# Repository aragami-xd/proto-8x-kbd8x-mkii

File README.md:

## Custom pcb for kbd8x-mkii based on my own personal preference

### Simplified version, less layout, less feature, more clean 

Any recommendations will be ignored and you will be banned, unless you point out fatal flaws in the pcb in which case you can stay

Insta ban if you mention iso support. I may or may not regret this when I find an iso alps board with good condition keycaps

Board dimension, layout and part of the schematics are based on [ai03's kbd8x-mkii's repo](https://github.com/ai03-2725/KBD8X-MKII-PCB), rp2040 routing and schematics are based on [sleepdealer's rpad](https://github.com/Sleepdealr/RPAD)

Todo list:
- ~~Swap out mcu for a different one like rp2040~~ (good luck finding at32u4 for cheap nowadays)
- Add jst connector for shits and giggles (if i can use it for something funny i can yeet out the brass weight and use it)
- ~~Possible alps support? if i can't get blue, amber or brown alps i can go for matias switches~~
- More meme cuts (maybe or maybe not)
- Make pcb thinner, 1.2mm? thinner pcb = easier to millmax / rivet
- ~~jis-alike layout~~: tried, not a good idea
- ~~aek layout~~: aek and 7u layout will be south facing, ~~standard 6.25u layout will be north facing~~ dropped standard layout
- ~~F1-8k layout: REMOVED, check **complex** version of the pcb~~

Layout supports:

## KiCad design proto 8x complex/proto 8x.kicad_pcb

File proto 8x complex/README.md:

## Custom pcb for kbd8x-mkii based on my own personal preference

### Complex version of the pcb, including all layouts supported (still no iso tho)

Any recommendations will be ignored and you will be banned, unless you point out fatal flaws in the pcb in which case you can stay

Insta ban if you mention iso support

Board dimension and layout is based on [ai03's kbd8x-mkii's repo](https://github.com/ai03-2725/KBD8X-MKII-PCB/blob/master), the rest has been reworked from scratch. All credits of the board goes to him and kbdfans

Todo list:
- ~~Swap out mcu for a different one like rp2040~~ (good luck finding at32u4 for cheap nowadays)
- Add jst connector for shits and giggles (if i can use it for something funny i can yeet out the brass weight and use it)
- ~~Possible alps support? if i can't get blue, amber or brown alps i can go for matias switches~~
- More meme cuts (maybe or maybe not)
- Make pcb thinner, 1.2mm? thinner pcb = easier to millmax / rivet
- ~~jis-alike layout~~: tried, not a good idea
- ~~aek layout~~: aek and 7u layout will be south facing, standard 6.25u layout will be north facing
- ~~F1-8k layout~~

Layout supports:

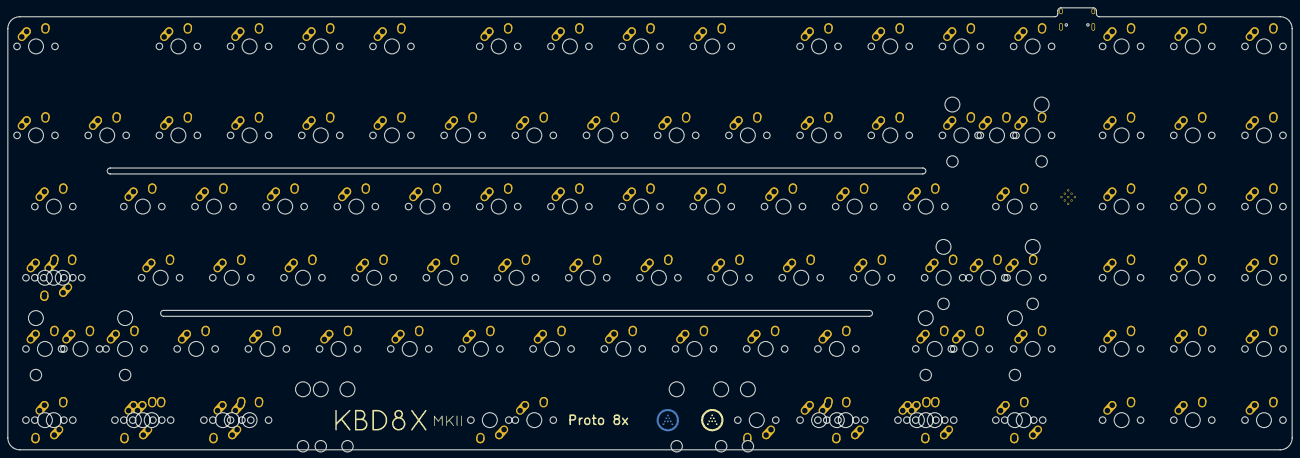
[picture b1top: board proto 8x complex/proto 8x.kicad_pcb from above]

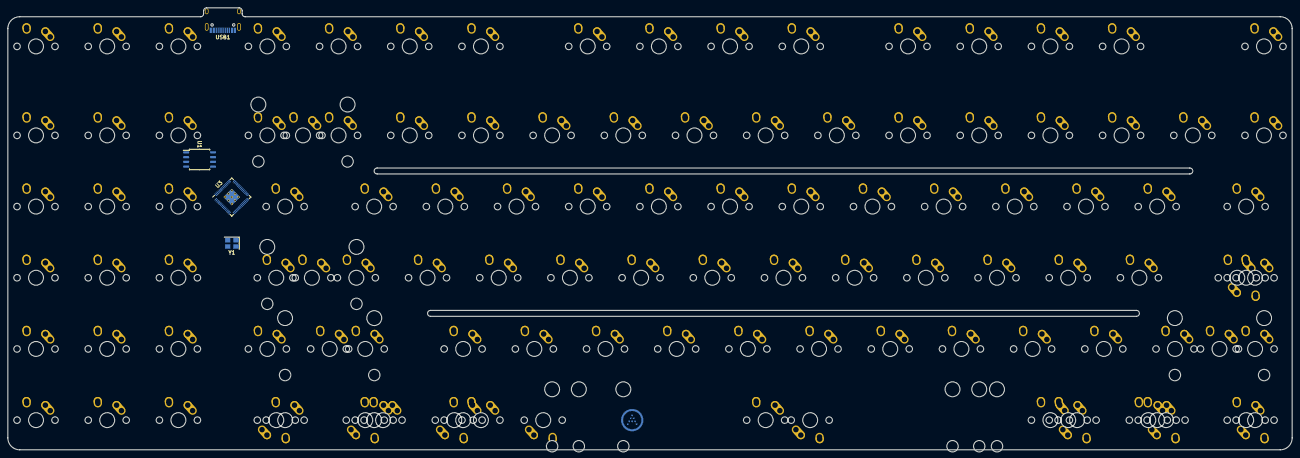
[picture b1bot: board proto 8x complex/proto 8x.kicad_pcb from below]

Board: 2 copper layers, 343.7 x 118.3 mm, 118 parts (4 on the bottom side), 6 nets, no tracks yet.

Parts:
MX_#0_1, MX_#1, MX_#2, MX_#3, MX_#4, MX_#5, MX_#6, MX_#7, MX_#8, MX_#9: MX-1U; MX-1U-NoLED
MX_'1: MX-1U; MX-1U-NoLED
MX_,1: MX-1U; MX-1U-NoLED
MX_-1: MX-1U; MX-1U-NoLED
MX_.1: MX-1U; MX-1U-NoLED
MX_/1: MX-1U; MX-1U-NoLED
MX_;1: MX-1U; MX-1U-NoLED
MX_=1: MX-1U; MX-1U-NoLED
MX_A1: MX-1U; MX-1U-NoLED
MX_B1: MX-1U; MX-1U-NoLED
MX_BACK1: MX-2U; MX-2U-ReversedStabilizers-NoLED
MX_BACK2, MX_BACK3: MX-1U; MX-1U-NoLED
MX_C1: MX-1U; MX-1U-NoLED
MX_CLOCK1: MX-1.75U; MX-1.75U-NoLED
MX_CLOCK2: MX-1.25U; MX-1.25U-NoLED
MX_CLOCK3: MX-1.5U; MX-1.5U-NoLED
MX_D1: MX-1U; MX-1U-NoLED
MX_DEL1_NP7: MX-1U; MX-1U-NoLED
MX_DN1_NP0: MX-1U; MX-1U-NoLED
MX_E1: MX-1U; MX-1U-NoLED
MX_END1_NP8: MX-1U; MX-1U-NoLED
MX_ESC1: MX-1U; MX-1U-NoLED
MX_F1: MX-1U; MX-1U-NoLED
MX_FN1, MX_FN2, MX_FN3, MX_FN4, MX_FN5, MX_FN6, MX_FN7, MX_FN8, MX_FN9, MX_FN10, MX_FN11, MX_FN12: MX-1U; MX-1U-NoLED
MX_G1: MX-1U; MX-1U-NoLED
MX_H1: MX-1U; MX-1U-NoLED
MX_HOME1: MX-1U; MX-1U-NoLED
MX_I1: MX-1U; MX-1U-NoLED
MX_INS1: MX-1U; MX-1U-NoLED
MX_J1: MX-1U; MX-1U-NoLED
MX_K1: MX-1U; MX-1U-NoLED
MX_L1: MX-1U; MX-1U-NoLED
MX_LALT1: MX-1.25U; MX-1.25U-NoLED
MX_LALT2, MX_LALT3: MX-1.5U; MX-1.5U-NoLED
MX_LCTRL1: MX-1.25U; MX-1.25U-NoLED
MX_LCTRL2: MX-1.5U; MX-1.5U-NoLED
MX_LFT1_NP00: MX-1U; MX-1U-NoLED
MX_LGUI1: MX-1.25U; MX-1.25U-NoLED
MX_LGUI2, MX_LGUI3: MX-1U; MX-1U-NoLED
MX_LSHIFT1: MX-2.25U; MX-2.25U-ReversedStabilizers-NoLED
MX_LSHIFT2: MX-1.25U; MX-1.25U-NoLED
MX_LSHIFT3: MX-1U; MX-1U-NoLED
MX_M1: MX-1U; MX-1U-NoLED
MX_N1: MX-1U; MX-1U-NoLED
MX_NP1, MX_NP3, MX_NP4, MX_NP5, MX_NP6: MX-1U; MX-1U-NoLED
MX_O1: MX-1U; MX-1U-NoLED
MX_P1: MX-1U; MX-1U-NoLED
MX_PAUSE1: MX-1U; MX-1U-NoLED
MX_PGDN1_NP9: MX-1U; MX-1U-NoLED
MX_PGUP1: MX-1U; MX-1U-NoLED
MX_PRINT1: MX-1U; MX-1U-NoLED
MX_Q1: MX-1U; MX-1U-NoLED
MX_R1: MX-1U; MX-1U-NoLED
MX_RALT1: MX-1.25U; MX-1.25U-NoLED
MX_RALT2, MX_RALT3: MX-1.5U; MX-1.5U-NoLED
MX_RCTRL1, MX_RCTRL3: MX-1.25U; MX-1.25U-NoLED
MX_RCTRL2: MX-1.5U; MX-1.5U-NoLED
MX_RETURN1: MX-2.25U; MX-2.25U-ReversedStabilizers-NoLED
MX_RGUI1: MX-1.25U; MX-1.25U-NoLED
MX_RGUI2, MX_RGUI3: MX-1U; MX-1U-NoLED
MX_RMENU1: MX-1.25U; MX-1.25U-NoLED
MX_RSHIFT1: MX-2.75U; MX-2.75U-ReversedStabilizers-NoLED
MX_RSHIFT2: MX-1.75U; MX-1.75U-NoLED
MX_RSHIFT3: MX-1U; MX-1U-NoLED
MX_RT1_NP_DOT: MX-1U; MX-1U-NoLED
MX_S1: MX-1U; MX-1U-NoLED
MX_SLOCK1: MX-1U; MX-1U-NoLED
MX_SP1: MX-6.25U; MX-6.25U-NoLED
MX_SP2: MX-7U; MX-7U-ReversedStabilizers-NoLED
MX_SP3: MX-7U; MX-6.5U-ReversedStabilizers-NoLED
MX_T1: MX-1U; MX-1U-NoLED
MX_TAB1: MX-1.5U; MX-1.5U-NoLED
MX_U1: MX-1U; MX-1U-NoLED
MX_UP1_NP2: MX-1U; MX-1U-NoLED
MX_V1: MX-1U; MX-1U-NoLED
MX_W1: MX-1U; MX-1U-NoLED
MX_X1: MX-1U; MX-1U-NoLED
MX_Y1: MX-1U; MX-1U-NoLED
MX_Z1: MX-1U; MX-1U-NoLED
MX_[1: MX-1U; MX-1U-NoLED
MX_\1: MX-1.5U; MX-1.5U-NoLED
MX_\2: MX-1U; MX-1U-NoLED
MX_]1: MX-1U; MX-1U-NoLED
MX_`1: MX-1U; MX-1U-NoLED
U1: W25Q128JVS; SOIC-8_5.23x5.23mm_P1.27mm
U3: RP2040; RP2040-QFN-56
USB1: HRO-TYPE-C-31-M-12; HRO-TYPE-C-31-M-12-Assembly
Y1: 12MHz; Crystal_SMD_3225-4Pin_3.2x2.5mm

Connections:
+1V1: U3.45 (VREG_VOUT), U3.50 (DVDD)
+3V3: U3.43 (ADC_AVDD), U3.44 (VREG_VIN), U3.48 (USB_VDD), U3.49 (IOVDD)
CS: U1.1 (~CS), U3.56 (QSPI_SS_N)
GND: U1.4 (GND), USB1.1, USB1.12, USB1.13
SD1: U1.2 (DO(IO1)), U3.55 (QSPI_SD1)
SD2: U1.3 (IO2), U3.54 (QSPI_SD2)

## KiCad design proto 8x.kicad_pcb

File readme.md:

### Custom pcb for kbd8x-mkii based on my own personal preference (i.e. stripped down, alps support and more layouts)

Any recommendations will be ignored and you will be banned, unless you point out fatal flaws in the pcb in which case you can stay

PCB keeps the same matrix as ai03's original matrix as much as possible

Insta ban if you mention iso support (if i decide to do it, it's gonna be for the BIG ASS enter, will consider yeeting out the split left shift in the future)

Based on [ai03's kbd8x-mkii's public repo pcb kicad file](https://github.com/ai03-2725/KBD8X-MKII-PCB/blob/master/KBD8X-MK2.kicad_pcb)

Todo list:
- Swap out mcu for a different one like rp2040 (good luck finding at32u4 for cheap)
- Add jst connector for shits and giggles (if i can use it for something funny i can yeet out the brass weight and use it)
- ~~Possible alps support? if i can't get blue,amber or brown alps i can go for matias switches~~
- More meme cuts (maybe or maybe not)
- Make pcb thinner, 1.2mm? thinner pcb = better pcb rivet hotswap socket support
- ~~jis-like layout (but not really jis, either 4.5u layout or minila 3u layout)~~: tried, not a good idea at all lemme tell ya, just look into the jis layout folder
- ~~aek layout~~ some aek or alps only layout will only be using alps only sockets (1.5u stepped caps lock, aek 6.5u bottom row). mx only layout will use mx only sockets (1.25u stepped caps lock, standard bottom row)

Update: 6.25u can work with aek layout, but the 6.25u will have to be north facing. If you're using 6.25u standard bottom row chances are you're not using gmk sbacepar anyways so less worry about tolerance? the other 2 layouts will share the same 7u spacebar position. and alps don't have north facing interference so if i get matias with taihao caps or something it'll be fine

Potential supported layouts (either 6.25u or aek only, not both):

q&a:
- Why no iso? cuz i don't like iso + iso compat plates suck (for enter & backslash key)
- Why no iso but still split lshift? idk 1 extra easy to access key for playing doom enternal ig? probably use that key for weapon mod swap instead of ctrl
- Why aek layout? in case i manage to harvest amber alps in an apple aek in the future
- Why 6.25u north facing? explained above ^
- Where the bottom flex cut? i'll add the wilba wt60d weirdflex-like flex cut in the future

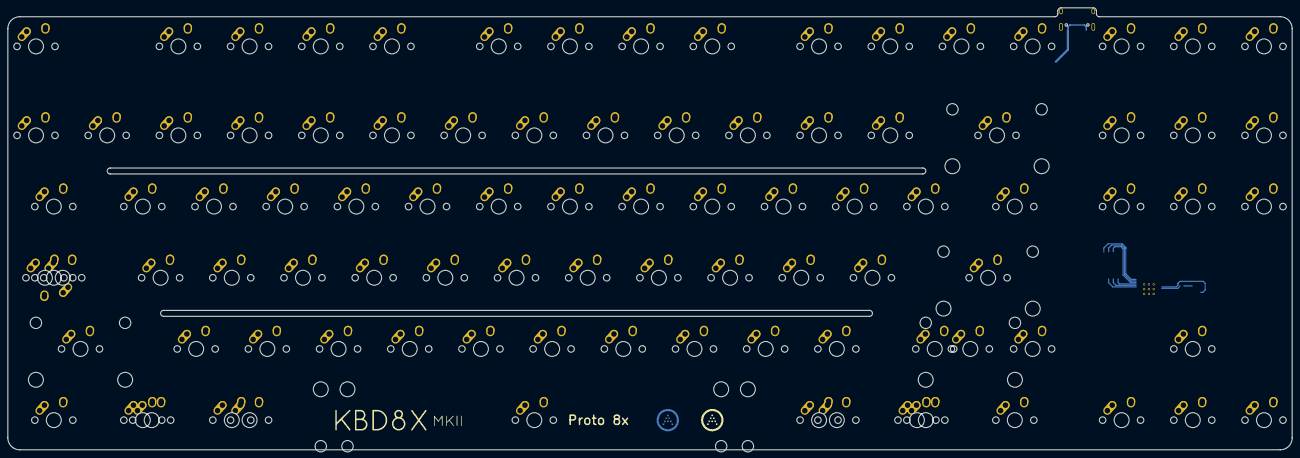
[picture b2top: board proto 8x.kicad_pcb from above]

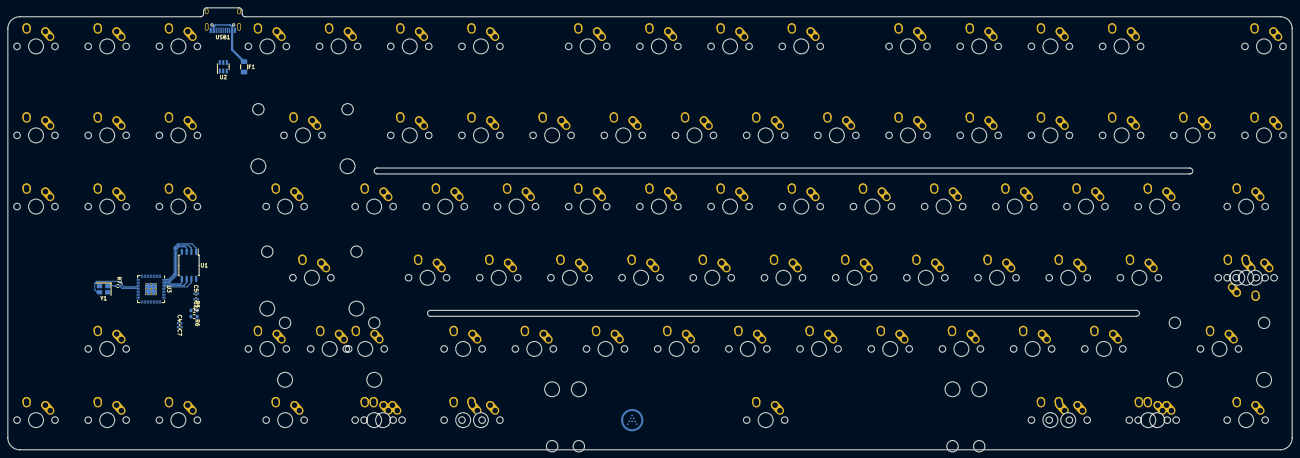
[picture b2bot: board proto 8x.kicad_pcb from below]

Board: 2 copper layers, 343.7 x 118.3 mm, 108 parts (13 on the bottom side), 13 nets.

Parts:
C4, C7: 1uF; C_0402_1005Metric
C5, C12: 100nF; C_0402_1005Metric
F1: 500mA; Fuse_1206_3216Metric
MX_#0_1, MX_#1, MX_#2, MX_#3, MX_#4, MX_#5, MX_#6, MX_#7, MX_#8, MX_#9: MX-1U; MX-1U-NoLED
MX_'1: MX-1U; MX-1U-NoLED
MX_,1: MX-1U; MX-1U-NoLED
MX_-1: MX-1U; MX-1U-NoLED
MX_.1: MX-1U; MX-1U-NoLED
MX_/1: MX-1U; MX-1U-NoLED
MX_;1: MX-1U; MX-1U-NoLED
MX_=1: MX-1U; MX-1U-NoLED
MX_A1: MX-1U; MX-1U-NoLED
MX_B1: MX-1U; MX-1U-NoLED
MX_BACK1: MX-2U; MX-2U-NoLED
MX_C1: MX-1U; MX-1U-NoLED
MX_CLOCK1: MX-1.75U; MX-1.75U-NoLED
MX_CLOCK2: MX-1.25U; MX-1.25U-NoLED
MX_CLOCK3: MX-1.5U; MX-1.5U-NoLED
MX_D1: MX-1U; MX-1U-NoLED
MX_DEL1_NP7: MX-1U; MX-1U-NoLED
MX_DN1_NP0: MX-1U; MX-1U-NoLED
MX_E1: MX-1U; MX-1U-NoLED
MX_END1_NP8: MX-1U; MX-1U-NoLED
MX_ESC1: MX-1U; MX-1U-NoLED
MX_F1: MX-1U; MX-1U-NoLED
MX_FN1, MX_FN2, MX_FN3, MX_FN4, MX_FN5, MX_FN6, MX_FN7, MX_FN8, MX_FN9, MX_FN10, MX_FN11, MX_FN12: MX-1U; MX-1U-NoLED
MX_G1: MX-1U; MX-1U-NoLED
MX_H1: MX-1U; MX-1U-NoLED
MX_HOME1: MX-1U; MX-1U-NoLED
MX_I1: MX-1U; MX-1U-NoLED
MX_INS1: MX-1U; MX-1U-NoLED
MX_J1: MX-1U; MX-1U-NoLED
MX_K1: MX-1U; MX-1U-NoLED
MX_L1: MX-1U; MX-1U-NoLED
MX_LALT2, MX_LALT3: MX-1.5U; MX-1.5U-NoLED
MX_LCTRL2: MX-1.5U; MX-1.5U-NoLED
MX_LFT1_NP00: MX-1U; MX-1U-NoLED
MX_LGUI2, MX_LGUI3: MX-1U; MX-1U-NoLED
MX_LSHIFT1: MX-2.25U; MX-2.25U-NoLED
MX_M1: MX-1U; MX-1U-NoLED
MX_N1: MX-1U; MX-1U-NoLED
MX_O1: MX-1U; MX-1U-NoLED
MX_P1: MX-1U; MX-1U-NoLED
MX_PAUSE1: MX-1U; MX-1U-NoLED
MX_PGDN1_NP9: MX-1U; MX-1U-NoLED
MX_PGUP1: MX-1U; MX-1U-NoLED
MX_PRINT1: MX-1U; MX-1U-NoLED
MX_Q1: MX-1U; MX-1U-NoLED
MX_R1: MX-1U; MX-1U-NoLED
MX_RALT2, MX_RALT3: MX-1.5U; MX-1.5U-NoLED
MX_RCTRL2: MX-1.5U; MX-1.5U-NoLED
MX_RETURN1: MX-2.25U; MX-2.25U-NoLED
MX_RGUI2, MX_RGUI3: MX-1U; MX-1U-NoLED
MX_RSHIFT1: MX-2.75U; MX-2.75U-NoLED
MX_RSHIFT2: MX-1.75U; MX-1.75U-NoLED
MX_RSHIFT3: MX-1U; MX-1U-NoLED
MX_RT1_NP_DOT: MX-1U; MX-1U-NoLED
MX_S1: MX-1U; MX-1U-NoLED
MX_SLOCK1: MX-1U; MX-1U-NoLED
MX_SP2: MX-7U; MX-7U-ReversedStabilizers-NoLED
MX_SP3: MX-7U; MX-6.5U-ReversedStabilizers-NoLED
MX_T1: MX-1U; MX-1U-NoLED
MX_TAB1: MX-1.5U; MX-1.5U-NoLED
MX_U1: MX-1U; MX-1U-NoLED
MX_UP1_NP2: MX-1U; MX-1U-NoLED
MX_V1: MX-1U; MX-1U-NoLED
MX_W1: MX-1U; MX-1U-NoLED
MX_X1: MX-1U; MX-1U-NoLED
MX_Y1: MX-1U; MX-1U-NoLED
MX_Z1: MX-1U; MX-1U-NoLED
MX_[1: MX-1U; MX-1U-NoLED
MX_\1: MX-1.5U; MX-1.5U-NoLED
MX_]1: MX-1U; MX-1U-NoLED
MX_`1: MX-1U; MX-1U-NoLED
R5, R6: 27R; R_0603_1608Metric
R7: 1k; R_0402_1005Metric
U1: W25Q128JVS; SOIC-8_5.23x5.23mm_P1.27mm
U2: USBLC6-2SC6; SOT-23-6
U3: RP2040; RP2040-QFN-56
USB1: HRO-TYPE-C-31-M-12; HRO-TYPE-C-31-M-12-Assembly
Y1: 12MHz; Crystal_SMD_3225-4Pin_3.2x2.5mm

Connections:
+1V1: C4.1, C5.1, U3.50 (DVDD)
+3V3: C7.1, C12.1, U1.8 (VCC)
CS: U1.1 (~CS), U3.56 (QSPI_SS_N)
GND: C4.2, C5.2, C7.2, C12.2, U1.4 (GND), U3.19 (TESTEN), USB1.1, USB1.12, USB1.13, Y1.2, Y1.4
QSPI_CLK: U1.6 (CLK), U3.52 (QSPI_SCLK)
SD0: U1.5 (DI(IO0)), U3.53 (QSPI_SD0)
SD1: U1.2 (DO(IO1)), U3.55 (QSPI_SD1)
SD2: U1.3 (IO2), U3.54 (QSPI_SD2)
SD3: U1.7 (IO3), U3.51 (QSPI_SD3)
VBUS: F1.1, USB1.2, USB1.11
XTAL_0: R7.1, Y1.1
XTAL_IN: U3.20 (XTAL_IN), Y1.3
XTAL_OUT: R7.2, U3.21 (XTAL_OUT)

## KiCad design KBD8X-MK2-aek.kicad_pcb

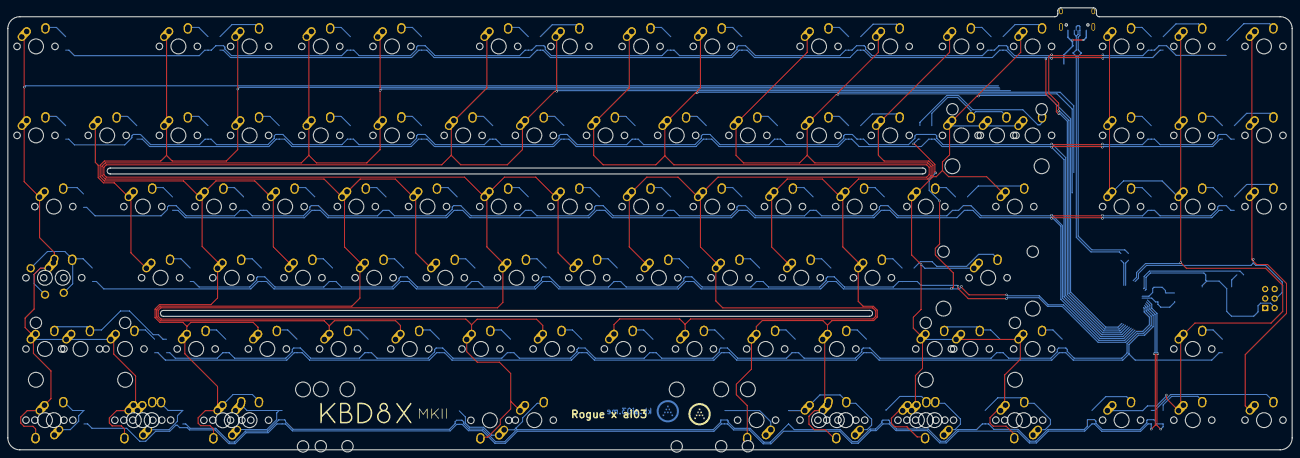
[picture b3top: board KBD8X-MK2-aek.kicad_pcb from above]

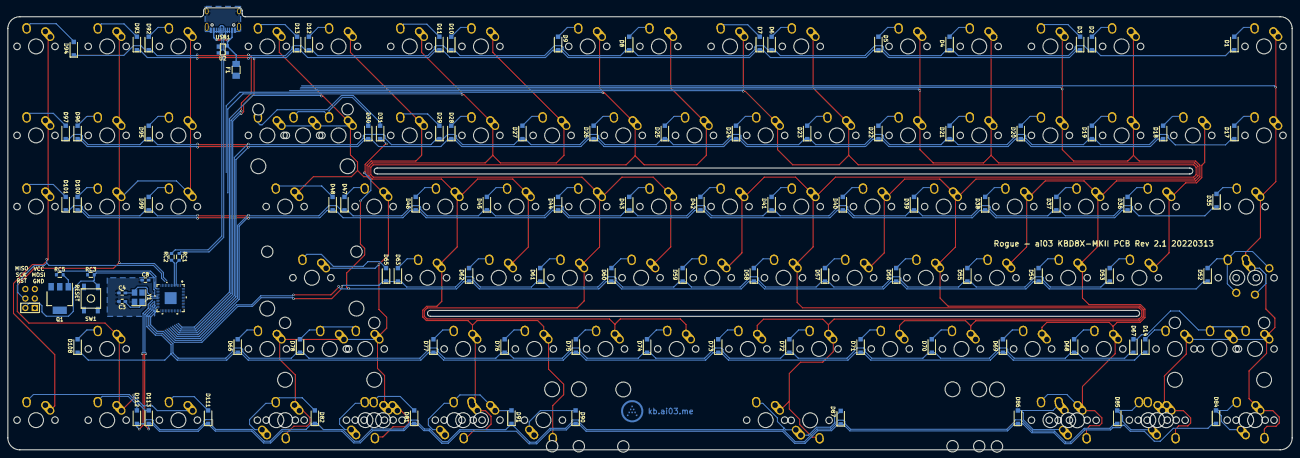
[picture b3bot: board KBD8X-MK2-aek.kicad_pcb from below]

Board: 2 copper layers, 343.7 x 118.3 mm, 211 parts (104 on the bottom side), 120 nets.

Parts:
C3, C4: 22pF; C_0603
C8: 0.1uF; C_0603
D1, D2, D3, D4, D5, D6, D7, D8, D9, D10, D11, D12, D13, D14, D17, D18, D19, D20, D21, D22, D23, D24, D25, D26, D27, D28, D29, D30, D31, D35, D36, D37, D38, D39, D40, D41, D42, D43, D44, D45, D46, D47, D48, D52, D53, D54, D55, D56, D57, D58, D59, D60, D61, D62, D63, D65, D66, D67, D68, D69, D70, D71, D72, D73, D74, D75, D76, D77, D78, D81, D82, D84, D85, D86, D87, D90, D91, D92, D93, D94, D95, D96, D97, D99, D100, D101, D108, D111, D112, D113: SOD-323; D_SOD-123
F1: 500mA; Fuse_SMD1206_Wave
J1: AVR-ISP-6; Reset_Pretty-Mask
MX_#0_1, MX_#1, MX_#2, MX_#3, MX_#4, MX_#5, MX_#6, MX_#7, MX_#8, MX_#9: MX-1U; MX-1U-NoLED
MX_'1: MX-1U; MX-1U-NoLED
MX_,1: MX-ALPS-1U; MX-1U-NoLED
MX_-1: MX-1U; MX-1U-NoLED
MX_.1: MX-ALPS-1U; MX-1U-NoLED
MX_/1: MX-ALPS-1U; MX-1U-NoLED
MX_;1: MX-1U; MX-1U-NoLED
MX_=1: MX-1U; MX-1U-NoLED
MX_A1: MX-ALPS-1U; MX-1U-NoLED
MX_B1: MX-ALPS-1U; MX-1U-NoLED
MX_BACK1: MX-2U; MX-2U-NoLED
MX_BACK2, MX_BACK3: MX-1U; MX-1U-NoLED
MX_C1: MX-ALPS-1U; MX-1U-NoLED
MX_CLOCK1: MX-1.75U; MX-1U-NoLED
MX_CLOCK2: MX-1.25U; MXOnly-1U-NoLED
MX_CLOCK2#2: MX-1.25U; ALPS-1U
MX_D1: MX-1U; MX-1U-NoLED
MX_DEL1: MX-1U; MX-1U-NoLED
MX_DN1: MX-1U; MX-1U-NoLED
MX_E1: MX-1U; MX-1U-NoLED
MX_END1: MX-1U; MX-1U-NoLED
MX_ESC1: MX-1U; MX-1U-NoLED
MX_F1: MX-1U; MX-1U-NoLED
MX_FN1, MX_FN2, MX_FN3, MX_FN4, MX_FN5, MX_FN6, MX_FN7, MX_FN8, MX_FN9, MX_FN10, MX_FN11, MX_FN12: MX-1U; MX-1U-NoLED
MX_G1: MX-1U; MX-1U-NoLED
MX_H1: MX-1U; MX-1U-NoLED
MX_HOME1: MX-1U; MX-1U-NoLED
MX_I1: MX-1U; MX-1U-NoLED
MX_INS1: MX-1U; MX-1U-NoLED
MX_J1: MX-1U; MX-1U-NoLED
MX_K1: MX-1U; MX-1U-NoLED
MX_L1: MX-1U; MX-1U-NoLED
MX_LALT1, MX_LALT2: MX-ALPS-1.5U; MX-1.5U-NoLED
MX_LCTRL1: MX-ALPS-1.5U; MX-1.5U-NoLED
MX_LCTRL1#2, MX_LCTRL1#3, MX_LCTRL1#4: MX-ALPS-1.5U; MX-1.25U-NoLED
MX_LFT1: MX-1U; MX-1U-NoLED
MX_LGUI1: MX-ALPS-1U; MX-1U-NoLED
MX_LGUI2: MX-ALPS-1.25U; MX-1.25U-NoLED
MX_LSHIFT1: MX-2.25U; MX-2.25U-NoLED
MX_LSHIFT2: MX-1.25U; MX-1.25U-NoLED
MX_LSHIFT3: MX-ALPS-1U; MX-1U-NoLED
MX_M1: MX-ALPS-1U; MX-1U-NoLED
MX_N1: MX-ALPS-1U; MX-1U-NoLED
MX_O1: MX-1U; MX-1U-NoLED
MX_P1: MX-1U; MX-1U-NoLED
MX_PAUSE1: MX-1U; MX-1U-NoLED
MX_PGDN1: MX-1U; MX-1U-NoLED
MX_PGUP1: MX-1U; MX-1U-NoLED
MX_PRINT1: MX-1U; MX-1U-NoLED
MX_Q1: MX-1U; MX-1U-NoLED
MX_R1: MX-1U; MX-1U-NoLED
MX_RALT1, MX_RALT2: MX-ALPS-1.5U; MX-1.5U-NoLED
MX_RCTRL1: MX-ALPS-1.5U; MX-1.5U-NoLED
MX_RCTRL1#2, MX_RCTRL1#3, MX_RCTRL1#4: MX-ALPS-1.5U; MX-1.25U-NoLED
MX_RCTRLe: MX-ALPS-1.5U; MX-1.25U-NoLED
MX_RETURN1: MX-2.25U; MX-2.25U-NoLED
MX_RGUI1: MX-ALPS-1U; MX-1U-NoLED
MX_RGUI2: MX-ALPS-1.25U; MX-1.25U-NoLED
MX_RSHIFT1: MX-2.75U; MX-2.75U-NoLED
MX_RSHIFT2: MX-1.75U; MX-1.75U-NoLED
MX_RSHIFT3: MX-1U; MX-1U-NoLED
MX_RT1: MX-1U; MX-1U-NoLED
MX_S1: MX-1U; MX-1U-NoLED
MX_SLOCK1: MX-1U; MX-1U-NoLED
MX_SP2: MX-7U; MX-7U-ReversedStabilizers-NoLED
MX_SP2#2: MX-7U; MX-6.5U-ReversedStabilizers-NoLED
MX_SP2#3: MX-7U; MX-6.25U-NoLED
MX_T1: MX-1U; MX-1U-NoLED
MX_TAB1: MX-1.5U; MX-1.5U-NoLED
MX_U1: MX-1U; MX-1U-NoLED
MX_UP1: MX-1U; MX-1U-NoLED
MX_V1: MX-ALPS-1U; MX-1U-NoLED
MX_W1: MX-1U; MX-1U-NoLED
MX_X1: MX-ALPS-1U; MX-1U-NoLED
MX_Y1: MX-1U; MX-1U-NoLED
MX_Z1: MX-ALPS-1U; MX-1U-NoLED
MX_[1: MX-1U; MX-1U-NoLED
MX_\1: MX-1.5U; MX-1.5U-NoLED
MX_]1: MX-1U; MX-1U-NoLED
MX_`1: MX-1U; MX-1U-NoLED
Q1: DSS60601MZ4-13; SOT-223-3_TabPin2
RC1, RC2: 22; R_0603
RC3: 10k; R_0603
RC5: 1.5k; R_0603
SW1: SW_Push; SKQG-1155865
U2: PRTR5V0U2X; SOT143B
USB1: HRO-TYPE-C-31-M-12; HRO-TYPE-C-31-M-12-Assembly
Y1: 16MHz; Crystal_SMD_3225-4pin_3.2x2.5mm

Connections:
+5V: C8.2, F1.1, J1.2, RC3.1
COL0: MX_#1.1, MX_A1.1, MX_CLOCK1.1, MX_CLOCK2.2, MX_ESC1.1, MX_LCTRL1.1, MX_LCTRL1#3.2, MX_LCTRL1#4.2, MX_LGUI1.1, MX_LGUI2.1, MX_LSHIFT1.1, MX_LSHIFT2.1, MX_LSHIFT3.1, MX_Q1.1, MX_TAB1.1, MX_`1.1
COL1: MX_#2.1, MX_#3.1, MX_D1.1, MX_E1.1, MX_FN1.1, MX_FN2.1, MX_LALT1.1, MX_LALT2.2, MX_LCTRL1#2.2, MX_S1.1, MX_W1.1, MX_X1.1, MX_Z1.1
COL2: MX_#4.1, MX_#5.1, MX_C1.1, MX_F1.1, MX_FN3.1, MX_FN4.1, MX_G1.1, MX_R1.1, MX_T1.1, MX_V1.1
COL3: MX_#6.1, MX_#7.1, MX_B1.1, MX_FN5.1, MX_FN6.1, MX_H1.1, MX_J1.1, MX_N1.1, MX_SP2.1, MX_SP2#3.2, MX_U1.1, MX_Y1.1
COL4: MX_#8.1, MX_#9.1, MX_,1.1, MX_FN7.1, MX_FN8.1, MX_I1.1, MX_K1.1, MX_L1.1, MX_M1.1, MX_O1.1
COL5: MX_#0_1.1, MX_'1.1, MX_-1.1, MX_.1.1, MX_/1.1, MX_;1.1, MX_FN9.1, MX_FN10.1, MX_P1.1, MX_RALT1.1, MX_RALT2.2, MX_RCTRL1#4.2, MX_RCTRLe.2, MX_[1.1
COL6: MX_=1.1, MX_BACK1.1, MX_BACK2.1, MX_BACK3.1, MX_FN11.1, MX_FN12.1, MX_RCTRL1.1, MX_RCTRL1#2.2, MX_RCTRL1#3.2, MX_RETURN1.1, MX_RGUI1.1, MX_RGUI2.1, MX_RSHIFT1.1, MX_RSHIFT2.1, MX_RSHIFT3.1, MX_\1.1, MX_]1.1
COL7: MX_DEL1.1, MX_DN1.1, MX_END1.1, MX_HOME1.1, MX_INS1.1, MX_LFT1.1, MX_PRINT1.1, MX_SLOCK1.1, MX_UP1.1
COL8: J1.3, MX_PAUSE1.1, MX_PGDN1.1, MX_PGUP1.1, MX_RT1.1
GND: C3.2, C4.2, C8.1, J1.6, Q1.3, SW1.1, U2.1, USB1.1, USB1.12, USB1.13, Y1.2, Y1.4
unnamed: D1.2, MX_ESC1.2
unnamed: D2.2, MX_FN1.2
unnamed: D3.2, MX_FN2.2
unnamed: D4.2, MX_FN3.2
unnamed: D5.2, MX_FN4.2
unnamed: D6.2, MX_FN5.2
unnamed: D7.2, MX_FN6.2
unnamed: D8.2, MX_FN7.2
unnamed: D9.2, MX_FN8.2
unnamed: D10.2, MX_FN9.2
unnamed: D11.2, MX_FN10.2
unnamed: D12.2, MX_FN11.2
unnamed: D13.2, MX_FN12.2
unnamed: D14.2, MX_LSHIFT3.2
unnamed: D17.2, MX_`1.2
unnamed: D18.2, MX_#1.2
unnamed: D19.2, MX_#2.2
unnamed: D20.2, MX_#3.2
unnamed: D21.2, MX_#4.2
unnamed: D22.2, MX_#5.2
unnamed: D23.2, MX_#6.2
unnamed: D24.2, MX_#7.2
unnamed: D25.2, MX_#8.2
unnamed: D26.2, MX_#9.2
unnamed: D27.2, MX_#0_1.2
unnamed: D28.2, MX_-1.2
unnamed: D29.2, MX_=1.2
unnamed: D30.2, MX_BACK1.2, MX_BACK2.2
unnamed: D31.2, MX_BACK3.2
unnamed: D35.2, MX_TAB1.2
unnamed: D36.2, MX_Q1.2
unnamed: D37.2, MX_W1.2
unnamed: D38.2, MX_E1.2
unnamed: D39.2, MX_R1.2
unnamed: D40.2, MX_T1.2
unnamed: D41.2, MX_Y1.2
unnamed: D42.2, MX_U1.2
unnamed: D43.2, MX_I1.2
unnamed: D44.2, MX_O1.2
unnamed: D45.2, MX_P1.2
unnamed: D46.2, MX_[1.2
unnamed: D47.2, MX_]1.2
unnamed: D48.2, MX_\1.2
unnamed: D52.2, MX_CLOCK1.2, MX_CLOCK2.1
unnamed: D53.2, MX_A1.2
unnamed: D54.2, MX_S1.2
unnamed: D55.2, MX_D1.2
unnamed: D56.2, MX_F1.2
unnamed: D57.2, MX_G1.2
unnamed: D58.2, MX_H1.2
unnamed: D59.2, MX_J1.2
unnamed: D60.2, MX_K1.2
unnamed: D61.2, MX_L1.2
unnamed: D62.2, MX_;1.2
unnamed: D63.2, MX_'1.2
unnamed: D65.2, MX_RETURN1.2
unnamed: D66.2, MX_RSHIFT3.2
unnamed: D67.2, MX_LSHIFT1.2, MX_LSHIFT2.2
unnamed: D68.2, MX_Z1.2
unnamed: D69.2, MX_X1.2
unnamed: D70.2, MX_C1.2
unnamed: D71.2, MX_V1.2
unnamed: D72.2, MX_B1.2
unnamed: D73.2, MX_N1.2
unnamed: D74.2, MX_M1.2
unnamed: D75.2, MX_,1.2
unnamed: D76.2, MX_.1.2
unnamed: D77.2, MX_/1.2
unnamed: D78.2, MX_RSHIFT1.2, MX_RSHIFT2.2
unnamed: D81.2, MX_RCTRL1#2.1, MX_RGUI1.2, MX_RGUI2.2
unnamed: D82.2, MX_RCTRL1.2, MX_RCTRL1#3.1
unnamed: D84.2, MX_LCTRL1.2, MX_LCTRL1#3.1
unnamed: D85.2, MX_LCTRL1#4.1, MX_LGUI1.2, MX_LGUI2.2
unnamed: D86.2, MX_LALT1.2, MX_LALT2.1, MX_LCTRL1#2.1
unnamed: D87.2, MX_SP2.2, MX_SP2#3.1
unnamed: D90.2, MX_RCTRL1#4.1
unnamed: D91.2, MX_RALT1.2, MX_RALT2.1, MX_RCTRLe.1
unnamed: D92.2, MX_PRINT1.2
unnamed: D93.2, MX_SLOCK1.2
unnamed: D94.2, MX_PAUSE1.2
unnamed: D95.2, MX_INS1.2
unnamed: D96.2, MX_HOME1.2
unnamed: D97.2, MX_PGUP1.2
unnamed: D99.2, MX_DEL1.2
unnamed: D100.2, MX_END1.2
unnamed: D101.2, MX_PGDN1.2
unnamed: D108.2, MX_UP1.2
unnamed: D111.2, MX_LFT1.2
unnamed: D112.2, MX_DN1.2
unnamed: D113.2, MX_RT1.2
unnamed: Q1.1, RC5.2
unnamed: RC1.2, U2.3, USB1.5, USB1.7
unnamed: RC2.1, U2.2, USB1.6, USB1.8
RESET: J1.5, RC3.2, SW1.2
ROW0: D1.1, D2.1, D4.1, D6.1, D8.1, D10.1, D12.1, D92.1, D94.1
ROW1: D3.1, D5.1, D7.1, D9.1, D11.1, D13.1, D93.1
ROW2: D17.1, D19.1, D21.1, D23.1, D25.1, D27.1, D29.1, D95.1, D97.1
ROW3: D18.1, D20.1, D22.1, D24.1, D26.1, D28.1, D30.1, D96.1
ROW4: D35.1, D37.1, D39.1, D41.1, D43.1, D45.1, D47.1, D99.1, D101.1
ROW5: D36.1, D38.1, D40.1, D42.1, D44.1, D46.1, D48.1, D100.1
ROW6: D31.1, D52.1, D54.1, D56.1, D58.1, D60.1, D62.1
ROW7: D53.1, D55.1, D57.1, D59.1, D61.1, D63.1, D65.1
ROW8: D67.1, D68.1, D70.1, D72.1, D74.1, D76.1, D78.1
ROW9: D14.1, D66.1, D69.1, D71.1, D73.1, D75.1, D77.1, D108.1
ROW10: D81.1, D84.1, D86.1, D87.1, D90.1, D111.1, D113.1
ROW11: D82.1, D85.1, D91.1, D112.1
VCC: F1.2, U2.4, USB1.2, USB1.11
XTAL1: C3.1, Y1.1
XTAL2: C4.1, Y1.3

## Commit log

2022-01-02 initial commit with pcb yeeted out all the leds but include non function components atm
2022-01-02 fix readme
2022-01-02 add pcb pics
2022-03-12 restart from scratch, change all to mx alps no led sockets, remote bottom flex cut
2022-03-12 update image + remove unrouted row 2 traces
2022-03-12 mx alps 2.75u shift, trim + prettify pcb
2022-03-13 clean up stuff
2022-03-18 add aek support + more documents
2022-03-19 remove aek layout since they're not compatible with 6.25u layout for now
2022-03-19 split into 2 pcbs
2022-03-19 route some bottom row stuff + add pads ratnest
2022-03-19 south facing standard, north facing aek bottom row, south facing alps caps lock
2022-03-20 route part of the right sides, cleanup, add possible jis support lol
2022-03-22 finish routing bottom row
2022-03-22 fix right bottom row to look even
2022-03-22 cleanup
2022-03-26 add schematic, changing to rp2040
2022-04-24 rev3 layout done, few components, no schematic rework yet
2022-04-24 add license
2022-04-26 move f1 + many split layout to complex version, add more board ocmponents
2022-05-07 retrace everything really, mcu and usb routing almost done
2022-05-07 update layout pic and images
2022-05-09 it's "done", i guess? needs a lot more cleanups
2022-05-09 add meme graphics

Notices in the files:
parts and their libraries:
Copyright 2021 Accelerated Designs. All rights reserved.
